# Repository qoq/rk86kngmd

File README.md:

# rk86kngmd

A replica of 1993 floppy disc controller for "Radio-86RK" computers. Built around i8255 PPI chip (Soviet clone: КР580ВВ55А) and a handful of discrete logic chips.

This version is a compact rework of the replica. 

- Compact layout
- 74LS series SOIC chips are used instead of DIP 555 logic
- Kept КР580ВВ55А and К155ИР13 as they are much easier to source than i8255 and 74LS198
- 28-pin ROM socket accepts 27C32 or 27C64 EPROM chips
- Added 34-pin standard floppy cable connector and 4-pin Berg power supply connector (+5v/+12v)
- Added AND circutry (2 diodes) to form ROM CS signal from CS1/CS2
- Added two bypass capacitors for stability

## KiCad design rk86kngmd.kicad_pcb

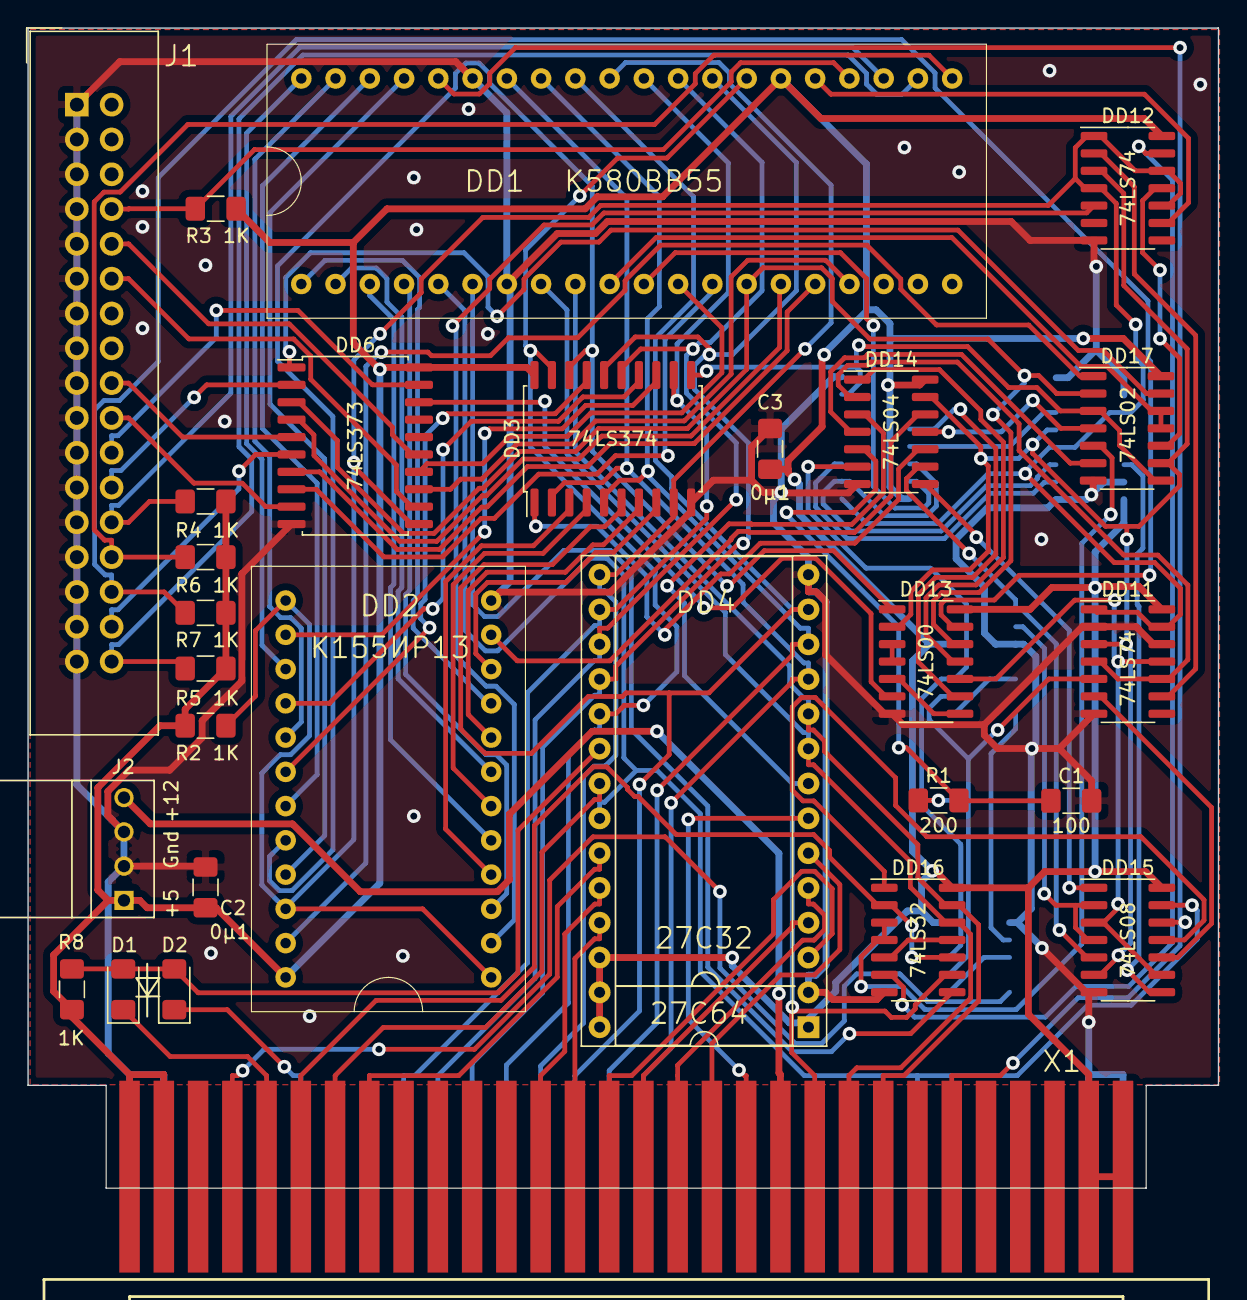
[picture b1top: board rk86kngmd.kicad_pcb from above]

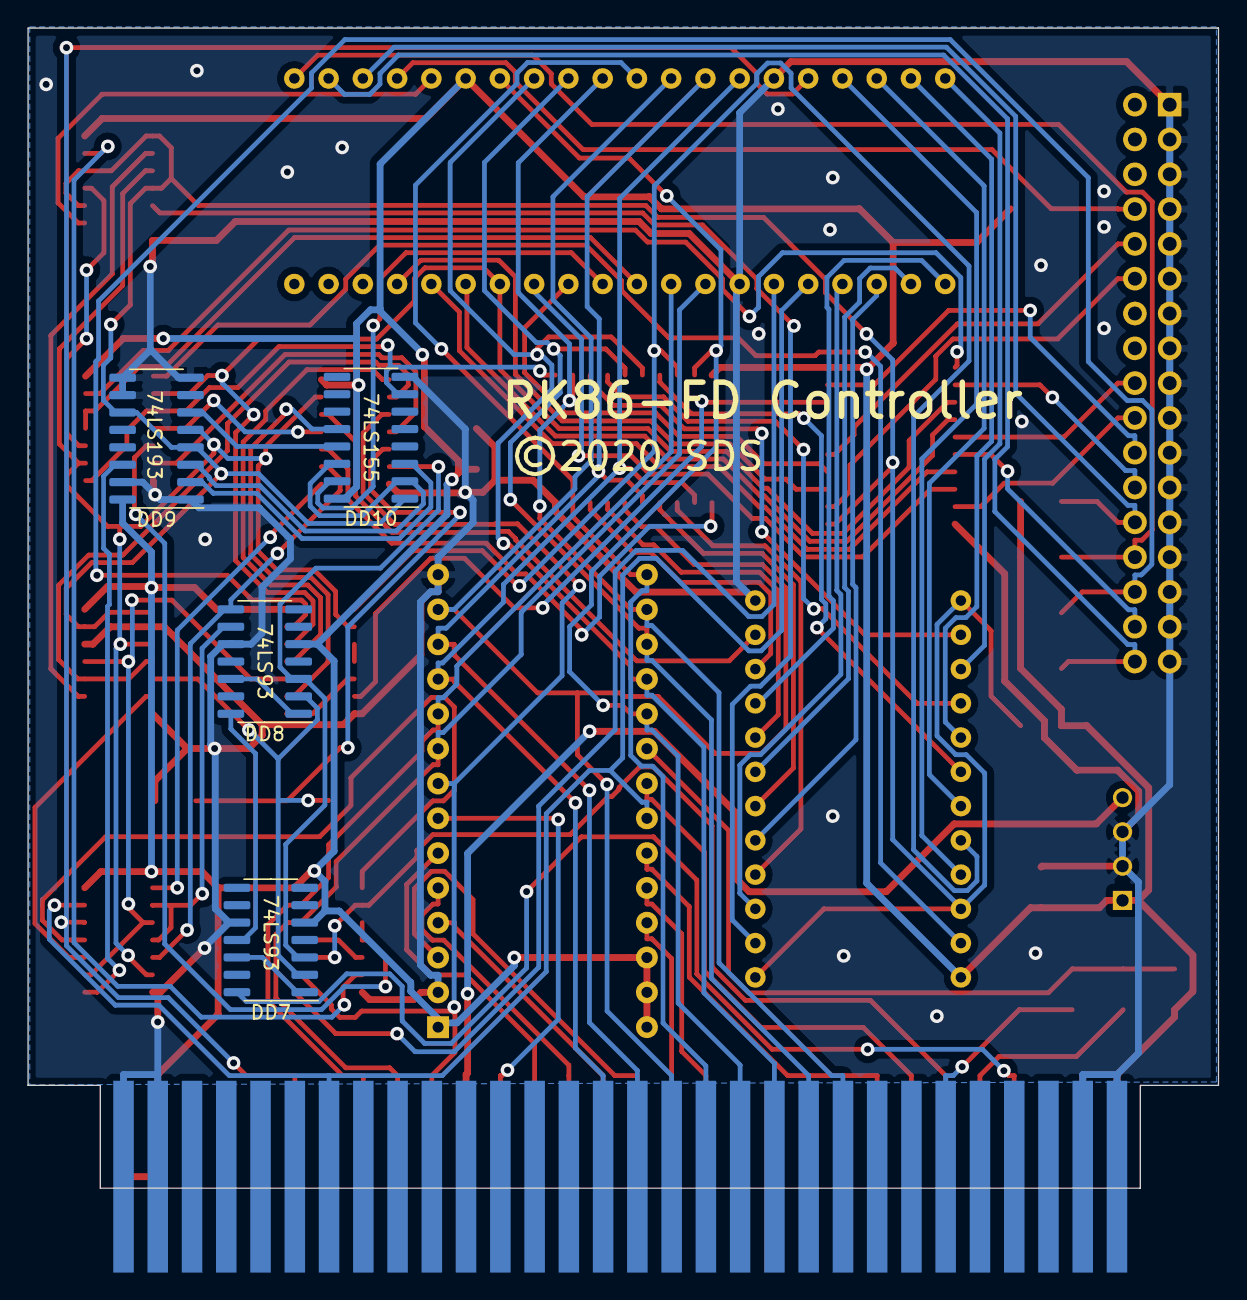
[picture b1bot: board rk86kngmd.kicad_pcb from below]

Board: 2 copper layers, 86.9 x 84.7 mm, 32 parts (4 on the bottom side), 105 nets.

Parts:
C1: 100; C_1206_3216Metric_Pad1.42x1.75mm_HandSolder
C2, C3: 0μ1; C_1206_3216Metric_Pad1.42x1.75mm_HandSolder
D1, D2: 2N4148; D_1206_3216Metric_Pad1.42x1.75mm_HandSolder
DD1: К580ВВ55; DIP40-2.5mm
DD2: К155ИР13; DIP24-2.5mm
DD3: 74LS374; SOIC-20W_7.5x12.8mm_P1.27mm
DD4: 27C64; DIP-28_W15.24mm_Socket
DD6: 74LS373; SOIC-20W_7.5x12.8mm_P1.27mm
DD7, DD8: 74LS93; SOIC-14_3.9x8.7mm_P1.27mm
DD9: 74LS193; SOIC-16_3.9x9.9mm_P1.27mm
DD10: 74LS155; SOIC-16_3.9x9.9mm_P1.27mm
DD11, DD12: 74LS74; SOIC-14_3.9x8.7mm_P1.27mm
DD13: 74LS00; SOIC-14_3.9x8.7mm_P1.27mm
DD14: 74LS04; SOIC-14_3.9x8.7mm_P1.27mm
DD15: 74LS08; SOIC-14_3.9x8.7mm_P1.27mm
DD16: 74LS32; SOIC-14_3.9x8.7mm_P1.27mm
DD17: 74LS02; SOIC-14_3.9x8.7mm_P1.27mm
J1: Conn_02x17_Odd_Even; IDC-Header_2x17_P2.54mm_Vertical
J2: FD power; TE_171826-4
R1: 200; R_1206_3216Metric_Pad1.42x1.75mm_HandSolder
R2, R3, R4, R5, R6, R7, R8: 1K; R_1206_3216Metric_Pad1.42x1.75mm_HandSolder
X1: ОНп-КС-23

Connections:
+5V: C2.1, C3.1, DD1.26, DD2.24, DD3.20, DD4.1, DD4.26, DD4.27, DD4.28, DD6.20, DD7.5, DD8.5, DD9.16, DD10.16, DD11.14, DD12.14, DD13.14, DD14.14, DD15.14, DD16.14, DD17.14, J2.1, R2.2, R3.1, R4.1, R5.1, R6.1, R7.1, R8.2, X1.B1, X1.B2, X1.B29, X1.B30
+12V: J2.4, X1.B11
/17: DD2.11, DD14.12
/18: DD3.1, DD14.10
/A0: DD1.9, DD4.10, DD16.13, X1.B8
/A1: DD1.8, DD4.9, DD16.12, X1.B9
/A2: DD4.8, DD14.3, DD16.9, X1.B10
/A3: DD4.7, X1.B12
/A4: DD4.6, X1.B13
/A5: DD4.5, X1.B14
/A6: DD4.4, X1.B15
/A7: DD4.3, X1.B16
/A8: DD4.25, X1.B17
/A9: DD4.24, X1.B18
/A10: DD4.21, X1.B24
/A11: DD4.23, X1.B23
/CS1: D1.1, X1.B26
/CS2: D2.1, X1.A25
/CS3: DD16.2, DD16.10, X1.B25
/CS12: D1.2, D2.2, DD4.20, R8.1
/D0: DD1.34, DD3.2, DD4.11, X1.A15
/D1: DD1.33, DD3.5, DD4.12, X1.A16
/D2: DD1.32, DD3.6, DD4.13, X1.A17
/D3: DD1.31, DD3.9, DD4.15, X1.A18
/D4: DD1.30, DD3.12, DD4.16, X1.A22
/D5: DD1.29, DD3.15, DD4.17, X1.A21
/D6: DD1.28, DD3.16, DD4.18, X1.A20
/D7: DD1.27, DD3.19, DD4.19, X1.A19
/OSC: DD7.14, X1.B27
/PB7: DD1.25, DD12.9
/PC1: DD1.15, DD6.4
/PC2: DD1.16, DD6.7
/PC3: DD1.17, DD6.13
/PC4: DD1.13, DD6.8
/PC5: DD1.12, DD6.14
/PC6: DD1.11, DD10.15
/PC7: DD1.10, DD17.11, DD17.12
/RD: DD1.5, DD4.22, DD15.13, X1.A7
/WR: DD1.36, DD15.12, X1.B6
/WRDATA: DD6.18, DD13.6
/WRGATE: DD1.14, DD6.3, DD13.12, DD17.2
DIR: DD6.5, J1.18
DISC_A: DD6.15, J1.10
DISC_B: DD6.12, J1.12
GND: C1.2, C2.2, C3.2, DD1.7, DD1.35, DD2.12, DD3.10, DD4.2, DD4.14, DD6.10, DD7.10, DD8.10, DD9.1, DD9.8, DD9.9, DD9.10, DD9.15, DD10.8, DD11.2, DD11.7, DD11.12, DD12.7, DD13.7, DD14.7, DD15.7, DD16.7, DD17.7, J1.1, J1.3, J1.5, J1.7, J1.9, J1.11, J1.13, J1.15, J1.17, J1.19, J1.21, J1.23, J1.25, J1.27, J1.29, J1.31, J1.33, J2.2, J2.3, X1.A1, X1.A2, X1.A29, X1.A30
IP: DD1.24, J1.8, R3.2
unnamed: C1.1, DD14.5, R1.2
unnamed: DD1.1, DD2.9
unnamed: DD1.2, DD2.7
unnamed: DD1.3, DD2.5
unnamed: DD1.4, DD2.3
unnamed: DD1.6, DD16.8
unnamed: DD1.37, DD2.21
unnamed: DD1.38, DD2.19
unnamed: DD1.39, DD2.17
unnamed: DD1.40, DD2.15
unnamed: DD2.4, DD3.3
unnamed: DD2.6, DD3.4
unnamed: DD2.8, DD3.7
unnamed: DD2.10, DD3.8
unnamed: DD2.14, DD3.13
unnamed: DD2.16, DD3.14
unnamed: DD2.18, DD3.17
unnamed: DD7.1, DD7.12
unnamed: DD7.11, DD8.14
unnamed: DD8.1, DD8.12
unnamed: DD2.1, DD2.13, DD2.22, DD6.11, DD9.4, DD9.11, DD10.1, DD11.1, DD11.13, DD12.1, DD12.4, DD12.10, DD12.12, R2.1
unnamed: DD9.2, DD10.3
unnamed: DD3.11, DD10.7, DD17.3, DD17.8
unnamed: DD10.12, DD13.9
unnamed: DD9.6, DD10.13
unnamed: DD9.3, DD10.2, DD10.14
unnamed: DD9.5, DD11.3, DD12.3, DD13.2, DD14.13, DD15.6, DD17.9
unnamed: DD7.2, DD8.2, DD11.5, R1.1
unnamed: DD11.6, DD15.10
unnamed: DD11.9, DD12.2
unnamed: DD11.4, DD11.10, DD14.2
unnamed: DD11.11, DD13.10, DD15.3, DD15.9
unnamed: DD2.2, DD12.5
unnamed: DD12.11, DD17.10
unnamed: DD12.13, DD16.6
unnamed: DD2.20, DD3.18, DD13.1
unnamed: DD13.3, DD13.4
unnamed: DD13.5, DD13.8
unnamed: DD13.11, DD14.1
unnamed: DD14.4, DD17.6
unnamed: DD7.3, DD8.3, DD14.6
unnamed: DD14.8, DD15.1
unnamed: DD8.8, DD14.9, DD15.5
unnamed: DD14.11, DD17.4
unnamed: DD8.9, DD15.2, DD15.4
unnamed: DD9.14, DD15.8
unnamed: DD15.11, DD16.1
unnamed: DD16.3, DD16.4, DD17.5
unnamed: DD16.5, DD16.11
unnamed: DD2.23, DD17.1
unnamed: DD6.1, DD17.13
RD_DATA: DD13.13, J1.30, R7.2
READY: DD1.22, J1.34, R5.2
SIDE: DD6.6, J1.32
STEP: DD6.9, J1.20
TR00: DD1.23, J1.26, R4.2
WPRT: DD1.21, J1.28, R6.2
WR_DATA: DD6.19, J1.22
WR_GATE: DD6.2, J1.24

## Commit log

2020-08-01 Combined ROM files
2020-08-01 Updated libraries
2020-08-02 board routed
2020-11-19 Switched to SMD components
2020-11-19 updated pictures
2020-12-19 minor updates

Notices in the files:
rk86kngmd.kicad_pcb:
©2020 SDS
